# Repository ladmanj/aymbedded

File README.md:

PCB for embed the AY-3-8910 and class-D amplifier into the ZX Spectrum+ case
2023/2024 Jakub Ladman
(ladmanj at volny cz)

For years I had a wire nest with a piece of protoboard for my AY-3-8910 (actually YM2149) that was very flimsy and prone to damage.
Last Christmas break I drew the PCB to put everything in the computer case.
The three PSG channels are mixed with the output of the SPKR ULA and the resulting signal is amplified by a class-D amplifier and sent to a reasonable quality loudspeaker.

All IOs used in the ZXS128k for serial ports are equipped with RS232 transceivers. The second IO port is connected directly to the optional connector.
These IO ports are not yet tested.

The PCB is soldered directly on the underside of the ZX Spectrum motherboard to the CPU pins.
The images are in the connection_instructions folder.

License: Do what you want. My support will be very limited, but feel free to ask me anything.

I have four blank PCBs. The first four of you can basically have it for the cost of shipping. Please contact me if you are interested.

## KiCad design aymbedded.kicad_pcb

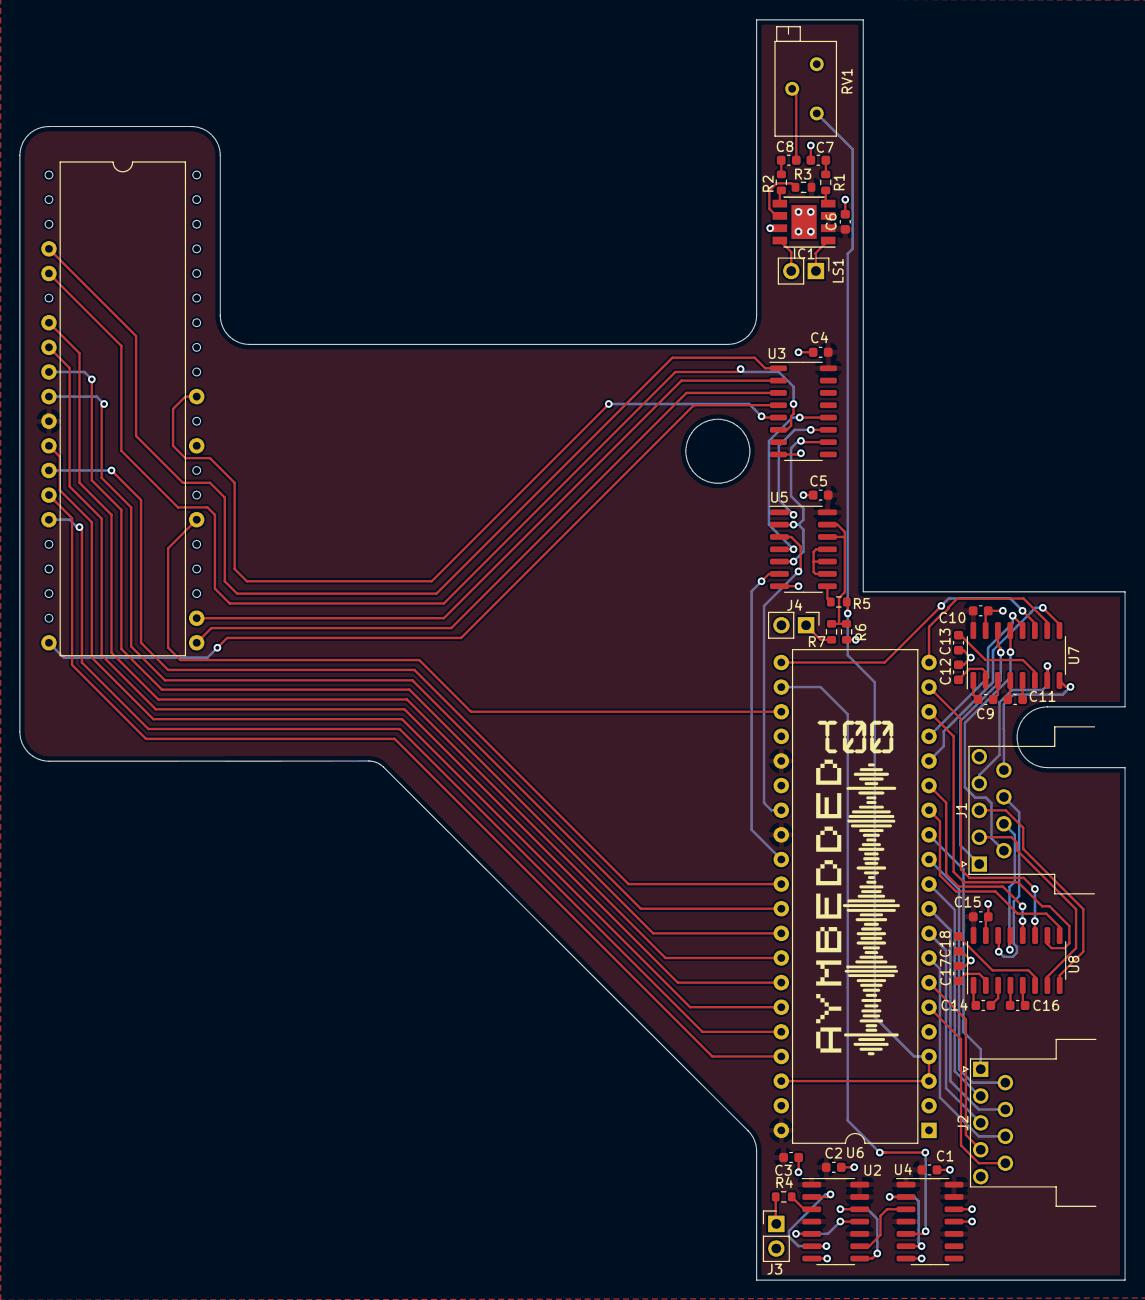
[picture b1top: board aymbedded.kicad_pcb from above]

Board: 2 copper layers, 114.0 x 130.0 mm, 40 parts (0 on the bottom side), 79 nets.

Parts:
C1, C2, C3, C4, C5, C6, C10, C15: 1uF; C_0603_1608Metric
C7, C8, C9, C11, C12, C13, C14, C16, C17, C18: 100n; C_0603_1608Metric
IC1: PAM8304ASR (CS8305E); Diodes_SO-8EP
J1: DE9_Plug; DSUB-9_Male_Horizontal_P2.77x2.54mm_EdgePinOffset9.40mm
J2: DE9_Receptacle; DSUB-9_Female_Horizontal_P2.77x2.54mm_EdgePinOffset9.40mm
J3, J4: Conn_01x02_Pin; PinHeader_1x02_P2.54mm_Vertical
LS1: Speaker; PinHeader_1x02_P2.54mm_Vertical
R1, R2, R5, R6, R7: 300k; R_0603_1608Metric
R3: 1k; R_0603_1608Metric
R4: 22R; R_0603_1608Metric
RV1: 10k; Potentiometer_Bourns_3299Z_Horizontal
U1: jen motiv na desce; DIP-40_W15.24mm
U2, U4: 74HC74; SO-14_3.9x8.65mm_P1.27mm
U3: 74HC138; SO-16_3.9x9.9mm_P1.27mm
U5: 74HC132; SO-14_3.9x8.65mm_P1.27mm
U6: AY-3-8910 (YM2149); DIP-40_W15.24mm
U7, U8: MAX3232; SO-16_3.9x9.9mm_P1.27mm

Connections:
/CLK_1.75MHz: U4.5 (Q), U6.22 (CLOCK)
/RS-232/R1: U6.17 (IOA4), U7.12 (R1OUT)
/RS-232/R2: U6.16 (IOA5), U7.9 (R2OUT)
/RS-232/RX1: J1.6, U7.13 (R1IN)
/RS-232/RX2: J1.9, U7.8 (R2IN)
/RS-232/T1: U6.21 (IOA0), U7.11 (T1IN)
/RS-232/T2: U6.20 (IOA1), U7.10 (T2IN)
/RS-232/TX1: J1.1, U7.14 (T1OUT)
/RS-232/TX2: J1.4, U7.7 (T2OUT)
/RS-233/R1: U6.15 (IOA6), U8.12 (R1OUT)
/RS-233/R2: U6.14 (IOA7), U8.9 (R2OUT)
/RS-233/RX1: J1.7, U8.13 (R1IN)
/RS-233/RX2: J1.3, U8.8 (R2IN)
/RS-233/T1: U6.19 (IOA2), U8.11 (T1IN)
/RS-233/T2: U6.18 (IOA3), U8.10 (T2IN)
/RS-233/TX1: J1.8, U8.14 (T1OUT)
/RS-233/TX2: J1.2, U8.7 (T2OUT)
/~RESET: U1.26 (~RESET), U6.23 (~RESET)
GND: C1.2, C2.2, C3.2, C4.2, C5.2, C6.2, C7.2, C10.1, C12.1, C13.1, C15.1, C17.1, C18.1, IC1.7 (GND), J1.5, J2.5, J3.2, J4.2, R6.1, RV1.3, U1.29 (GND), U2.7 (GND), U3.8 (GND), U4.7 (GND), U4.11 (C), U4.12 (D), U5.7 (GND), U6.1 (VSS), U7.15 (GND), U8.15 (GND)
unnamed: C7.1, R1.1
unnamed: C8.1, R2.1
unnamed: C8.2, RV1.2
unnamed: IC1.5 (IN+), R2.2
unnamed: IC1.4 (IN-), R1.2
unnamed: IC1.1 (OUT+), LS1.1
unnamed: IC1.8 (OUT-), LS1.2
unnamed: IC1.6 (~SD), R3.2
unnamed: J3.1, R4.2
unnamed: J4.1, R7.2
unnamed: R5.2, U5.8
unnamed: R6.2, R7.1, U5.12, U5.13
unnamed: U1.31 (A1), U3.5 (~E1)
unnamed: U1.4 (A14), U3.1 (A0)
unnamed: U1.5 (A15), U3.6 (E2)
unnamed: U1.14 (D0), U6.37 (DA0)
unnamed: U1.15 (D1), U6.36 (DA1)
unnamed: U1.12 (D2), U6.35 (DA2)
unnamed: U1.8 (D3), U6.34 (DA3)
unnamed: U1.7 (D4), U6.33 (DA4)
unnamed: U1.9 (D5), U6.32 (DA5)
unnamed: U1.10 (D6), U6.31 (DA6)
unnamed: U1.13 (D7), U6.30 (DA7)
unnamed: U1.20 (~IORQ), U3.4 (~E0)
unnamed: U1.21 (~RD), U3.3 (A2)
unnamed: U1.22 (~WR), U3.2 (A1)
unnamed: R4.1, U2.3 (C)
unnamed: U2.2 (D), U2.6 (~Q)
unnamed: U2.5 (Q), U2.11 (C)
unnamed: U2.8 (~Q), U2.12 (D)
unnamed: U2.9 (Q), U4.3 (C)
unnamed: U3.12 (~Y3), U5.4
unnamed: U3.11 (~Y4), U5.1
unnamed: U3.10 (~Y5), U5.2, U5.5
unnamed: U4.2 (D), U4.6 (~Q)
unnamed: U5.9, U5.10, U5.11
unnamed: R5.1, RV1.1, U6.3 (A), U6.4 (B), U6.38 (C)
unnamed: U5.6, U6.29 (BC1)
unnamed: U5.3, U6.27 (BDIR)
unnamed: J2.1, U6.13 (IOB0)
unnamed: J2.6, U6.12 (IOB1)
unnamed: J2.2, U6.11 (IOB2)
unnamed: J2.7, U6.10 (IOB3)
unnamed: J2.3, U6.9 (IOB4)
unnamed: J2.8, U6.8 (IOB5)
unnamed: J2.4, U6.7 (IOB6)
unnamed: J2.9, U6.6 (IOB7)
unnamed: C9.1, U7.1 (C1+)
unnamed: C9.2, U7.3 (C1-)
unnamed: C11.1, U7.4 (C2+)
unnamed: C11.2, U7.5 (C2-)
unnamed: C12.2, U7.2 (VS+)
unnamed: C13.2, U7.6 (VS-)
unnamed: C14.1, U8.1 (C1+)
unnamed: C14.2, U8.3 (C1-)
unnamed: C16.1, U8.4 (C2+)
unnamed: C16.2, U8.5 (C2-)
unnamed: C17.2, U8.2 (VS+)
unnamed: C18.2, U8.6 (VS-)
VCC: C1.1, C2.1, C3.1, C4.1, C5.1, C6.1, C10.2, C15.2, IC1.2 (PVDD), IC1.3 (VDD), R3.1, U1.11 (VCC), U2.1 (~R), U2.4 (~S), U2.10 (~S), U2.13 (~R), U2.14 (VCC), U3.16 (VCC), U4.1 (~R), U4.4 (~S), U4.10 (~S), U4.13 (~R), U4.14 (VCC), U5.14 (VCC), U6.25 (A8), U6.28 (BC2), U6.40 (VCC), U7.16 (VCC), U8.16 (VCC)

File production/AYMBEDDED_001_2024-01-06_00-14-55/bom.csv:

Designator,Footprint,Quantity,Value,LCSC Part #
"C1, C10, C15, C2, C3, C4, C5, C6",0603,8,1uF,
"C11, C12, C13, C14, C16, C17, C18, C7, C8, C9",0603,10,100n,
IC1,Diodes_SO-8EP,1,PAM8304ASR (CS8305E),
J1,DSUB-9_Male_Horizontal_P2.77x2.54mm_EdgePinOffset9.40mm,1,DE9_Plug,
J2,DSUB-9_Female_Horizontal_P2.77x2.54mm_EdgePinOffset9.40mm,1,DE9_Receptacle,
"J3, J4",PinHeader_1x02_P2.54mm_Vertical,2,Conn_01x02_Pin,
LS1,PinHeader_1x02_P2.54mm_Vertical,1,Speaker,
"R1, R2, R5, R6, R7",0603,5,300k,
R3,0603,1,1k,
R4,0603,1,22R,
RV1,Potentiometer_Bourns_3299Z_Horizontal,1,10k,
U1,DIP-40_W15.24mm,1,jen motiv na desce,
"U2, U4",SO-14_3.9x8.65mm_P1.27mm,2,74HC74,
U3,SO-16_3.9x9.9mm_P1.27mm,1,74HC138,
U5,SO-14_3.9x8.65mm_P1.27mm,1,74HC132,
U6,DIP-40_W15.24mm,1,AY-3-8910 (YM2149),
"U7, U8",SO-16_3.9x9.9mm_P1.27mm,2,MAX3232,

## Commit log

2024-01-26 PCB to embed AY-3-8910 and Class-D amplifier into ZX Spectrum+ case
2024-01-26 Create README.md
    Basic Instructions
2024-01-26 KiCAD 3D render added
2024-01-26 New picture
2024-01-26 Schematic in pdf format added
2024-02-01 Update README.md
    typos fixed
